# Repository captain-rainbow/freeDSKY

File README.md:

# freeDSKY
My open source DSKY replica that works with ReEntry: an orbital simulator.

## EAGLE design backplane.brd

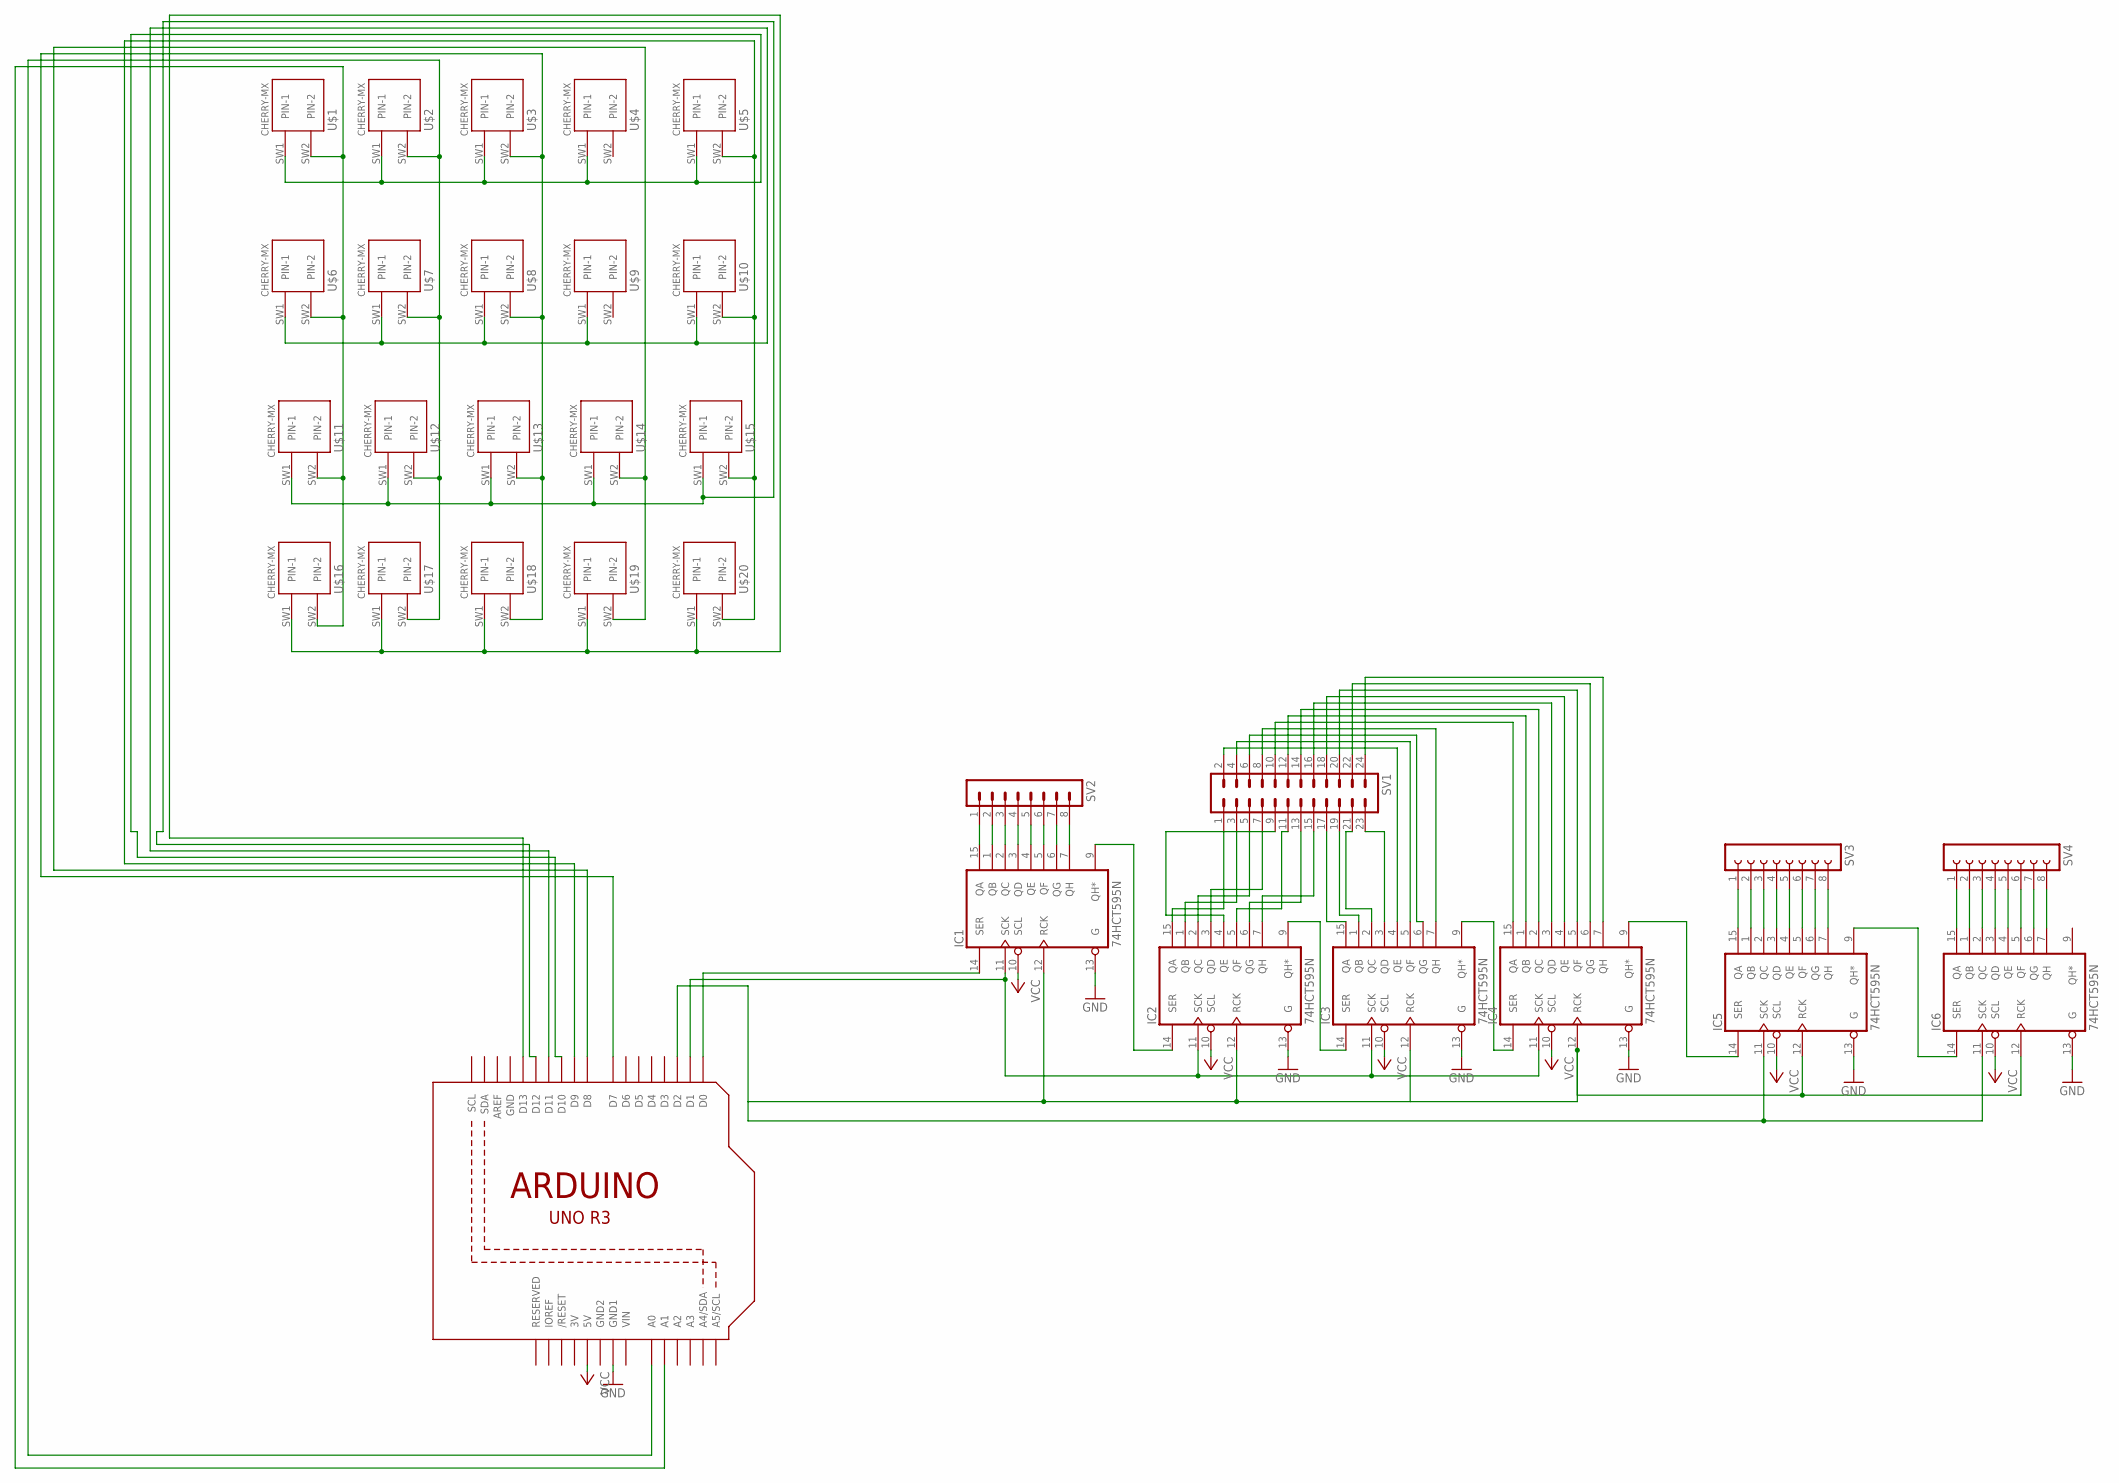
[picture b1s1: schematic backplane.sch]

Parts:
IC1, IC2, IC3, IC4, IC5, IC6: 74HCT595N; DIL16
SV1: MA12-2
SV2: MA08-1
SV3, SV4: FE08-1; FE08
U1: ARDUINOR3-BPLACE
U$1, U$2, U$3, U$4, U$5, U$6, U$7, U$8, U$9, U$10, U$11, U$12, U$13, U$14, U$15, U$16, U$17, U$18, U$19, U$20: CHERRY-MX

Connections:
3V: U1.3V
GND: IC1.8 (GND), IC1.13 (G), IC2.8 (GND), IC2.13 (G), IC3.8 (GND), IC3.13 (G), IC4.8 (GND), IC4.13 (G), IC5.8 (GND), IC5.13 (G), IC6.8 (GND), IC6.13 (G), U1.GND, U1.GND1
GND2: U1.GND2
unnamed: U1.D10, U$1.SW1 (PIN-1), U$2.SW1 (PIN-1), U$3.SW1 (PIN-1), U$4.SW1 (PIN-1), U$5.SW1 (PIN-1)
unnamed: U1.D11, U$6.SW1 (PIN-1), U$7.SW1 (PIN-1), U$8.SW1 (PIN-1), U$9.SW1 (PIN-1), U$10.SW1 (PIN-1)
unnamed: U1.D12, U$11.SW1 (PIN-1), U$12.SW1 (PIN-1), U$13.SW1 (PIN-1), U$14.SW1 (PIN-1), U$15.SW1 (PIN-1)
unnamed: U1.A1, U$1.SW2 (PIN-2), U$6.SW2 (PIN-2), U$11.SW2 (PIN-2), U$16.SW2 (PIN-2)
unnamed: U1.A0, U$2.SW2 (PIN-2), U$7.SW2 (PIN-2), U$12.SW2 (PIN-2), U$17.SW2 (PIN-2)
unnamed: U1.D7, U$3.SW2 (PIN-2), U$8.SW2 (PIN-2), U$13.SW2 (PIN-2), U$18.SW2 (PIN-2)
unnamed: U1.D8, U$14.SW2 (PIN-2), U$19.SW2 (PIN-2)
unnamed: U1.D9, U$5.SW2 (PIN-2), U$10.SW2 (PIN-2), U$15.SW2 (PIN-2), U$20.SW2 (PIN-2)
unnamed: IC3.5 (QF), SV1.4
unnamed: U1.D13, U$16.SW1 (PIN-1), U$17.SW1 (PIN-1), U$18.SW1 (PIN-1), U$19.SW1 (PIN-1), U$20.SW1 (PIN-1)
unnamed: IC3.6 (QG), SV1.6
unnamed: IC3.7 (QH), SV1.8
unnamed: IC2.15 (QA), SV1.1
unnamed: IC2.1 (QB), SV1.3
unnamed: IC2.2 (QC), SV1.5
unnamed: IC2.3 (QD), SV1.7
unnamed: IC2.4 (QE), SV1.9
unnamed: IC2.5 (QF), SV1.11
unnamed: IC2.6 (QG), SV1.13
unnamed: IC2.7 (QH), SV1.15
unnamed: IC3.15 (QA), SV1.17
unnamed: IC3.1 (QB), SV1.19
unnamed: IC3.2 (QC), SV1.21
unnamed: IC3.3 (QD), SV1.23
unnamed: IC3.4 (QE), SV1.2
unnamed: IC4.15 (QA), SV1.10
unnamed: IC4.1 (QB), SV1.12
unnamed: IC4.2 (QC), SV1.14
unnamed: IC4.3 (QD), SV1.16
unnamed: IC4.4 (QE), SV1.18
unnamed: IC4.5 (QF), SV1.20
unnamed: IC4.6 (QG), SV1.22
unnamed: IC4.7 (QH), SV1.24
unnamed: IC1.15 (QA), SV2.1
unnamed: IC1.1 (QB), SV2.2
unnamed: IC1.2 (QC), SV2.3
unnamed: IC1.3 (QD), SV2.4
unnamed: IC1.4 (QE), SV2.5
unnamed: IC1.5 (QF), SV2.6
unnamed: IC1.6 (QG), SV2.7
unnamed: IC1.7 (QH), SV2.8
unnamed: IC1.9 (QH*), IC2.14 (SER)
unnamed: IC2.9 (QH*), IC3.14 (SER)
unnamed: IC3.9 (QH*), IC4.14 (SER)
unnamed: IC1.14 (SER), U1.D0
unnamed: IC1.11 (SCK), IC2.11 (SCK), IC3.11 (SCK), IC4.11 (SCK), U1.D1
unnamed: IC5.15 (QA), SV3.1
unnamed: IC1.12 (RCK), IC2.12 (RCK), IC3.12 (RCK), IC4.12 (RCK), IC5.11 (SCK), IC5.12 (RCK), IC6.11 (SCK), IC6.12 (RCK), U1.D2
unnamed: IC5.1 (QB), SV3.2
unnamed: IC5.2 (QC), SV3.3
unnamed: IC5.3 (QD), SV3.4
unnamed: IC5.4 (QE), SV3.5
unnamed: IC5.5 (QF), SV3.6
unnamed: IC5.6 (QG), SV3.7
unnamed: IC5.7 (QH), SV3.8
unnamed: IC6.15 (QA), SV4.1
unnamed: IC6.1 (QB), SV4.2
unnamed: IC6.2 (QC), SV4.3
unnamed: IC6.3 (QD), SV4.4
unnamed: IC6.4 (QE), SV4.5
unnamed: IC6.5 (QF), SV4.6
unnamed: IC6.6 (QG), SV4.7
unnamed: IC6.7 (QH), SV4.8
unnamed: IC5.9 (QH*), IC6.14 (SER)
unnamed: IC4.9 (QH*), IC5.14 (SER)
VCC: IC1.10 (SCL), IC1.16 (VCC), IC2.10 (SCL), IC2.16 (VCC), IC3.10 (SCL), IC3.16 (VCC), IC4.10 (SCL), IC4.16 (VCC), IC5.10 (SCL), IC5.16 (VCC), IC6.10 (SCL), IC6.16 (VCC), U1.5V
VIN: U1.VIN

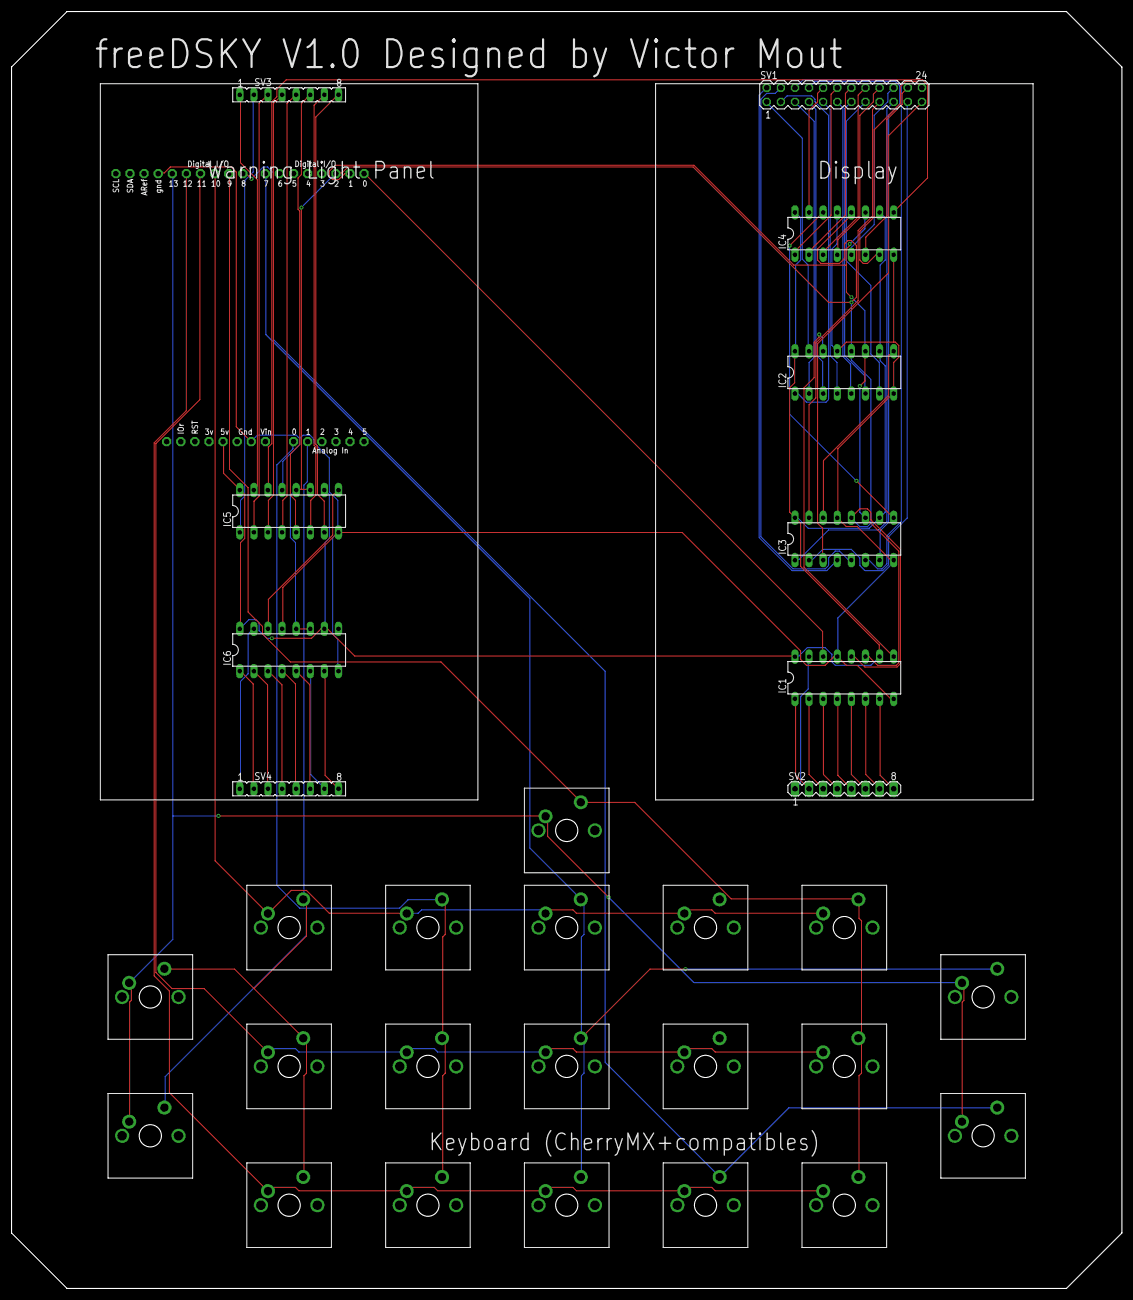
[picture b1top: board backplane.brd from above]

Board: 2 copper layers, 200.0 x 230.0 mm, 31 parts (0 on the bottom side), 67 nets.

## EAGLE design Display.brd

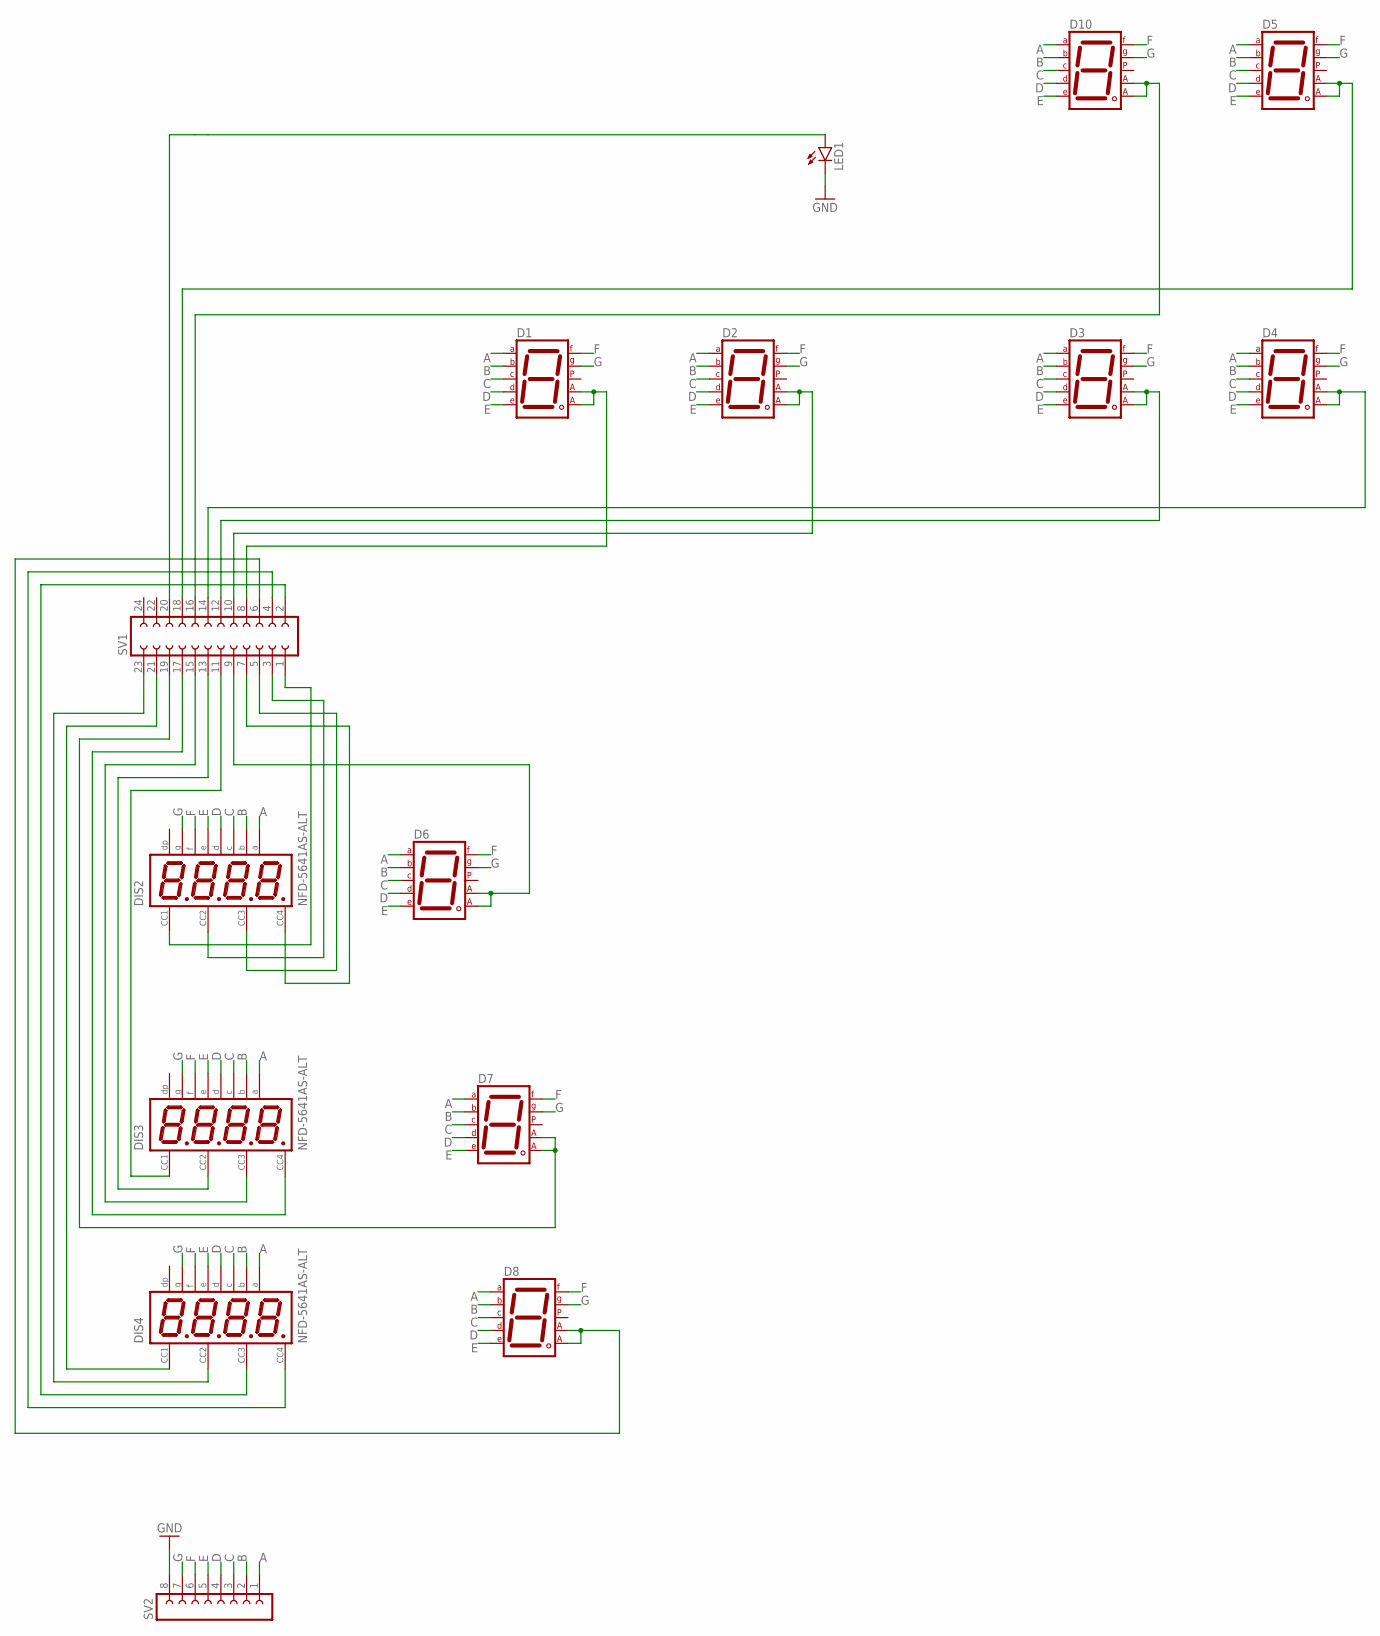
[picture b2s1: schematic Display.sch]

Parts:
D1, D2, D3, D4, D5, D6, D7, D8, D10: 7SEG-CA; 7SEG-13
DIS2, DIS3, DIS4: NFD-5641AS-ALT; NFD-5641
LED1: LED5MM
SV1: FE12-2
SV2: FE08-1; FE08

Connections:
A: D1.7 (A), D2.7 (A), D3.7 (A), D4.7 (A), D5.7 (A), D6.7 (A), D7.7 (A), D8.7 (A), D10.7 (A), DIS2.P$11, DIS3.P$11, DIS4.P$11, SV2.1
B: D1.6 (B), D2.6 (B), D3.6 (B), D4.6 (B), D5.6 (B), D6.6 (B), D7.6 (B), D8.6 (B), D10.6 (B), DIS2.P$7, DIS3.P$7, DIS4.P$7, SV2.2
C: D1.4 (C), D2.4 (C), D3.4 (C), D4.4 (C), D5.4 (C), D6.4 (C), D7.4 (C), D8.4 (C), D10.4 (C), DIS2.P$4, DIS3.P$4, DIS4.P$4, SV2.3
D: D1.2 (D), D2.2 (D), D3.2 (D), D4.2 (D), D5.2 (D), D6.2 (D), D7.2 (D), D8.2 (D), D10.2 (D), DIS2.P$2, DIS3.P$2, DIS4.P$2, SV2.4
E: D1.1 (E), D2.1 (E), D3.1 (E), D4.1 (E), D5.1 (E), D6.1 (E), D7.1 (E), D8.1 (E), D10.1 (E), DIS2.P$1, DIS3.P$1, DIS4.P$1, SV2.5
F: D1.9 (F), D2.9 (F), D3.9 (F), D4.9 (F), D5.9 (F), D6.9 (F), D7.9 (F), D8.9 (F), D10.9 (F), DIS2.P$10, DIS3.P$10, DIS4.P$10, SV2.6
G: D1.10 (G), D2.10 (G), D3.10 (G), D4.10 (G), D5.10 (G), D6.10 (G), D7.10 (G), D8.10 (G), D10.10 (G), DIS2.P$5, DIS3.P$5, DIS4.P$5, SV2.7
GND: LED1.K (C), SV2.8
unnamed: DIS2.P$12, SV1.1
unnamed: DIS2.P$9, SV1.3
unnamed: DIS2.P$8, SV1.5
unnamed: DIS2.P$6, SV1.7
unnamed: D6.3 (CA1), D6.8 (CA2), SV1.9
unnamed: DIS3.P$12, SV1.11
unnamed: DIS3.P$9, SV1.13
unnamed: DIS3.P$8, SV1.15
unnamed: DIS3.P$6, SV1.17
unnamed: D7.3 (CA1), D7.8 (CA2), SV1.19
unnamed: DIS4.P$12, SV1.21
unnamed: DIS4.P$9, SV1.23
unnamed: DIS4.P$8, SV1.2
unnamed: DIS4.P$6, SV1.4
unnamed: D1.3 (CA1), D1.8 (CA2), SV1.8
unnamed: D8.3 (CA1), D8.8 (CA2), SV1.6
unnamed: D2.3 (CA1), D2.8 (CA2), SV1.10
unnamed: D3.3 (CA1), D3.8 (CA2), SV1.12
unnamed: D4.3 (CA1), D4.8 (CA2), SV1.14
unnamed: D10.3 (CA1), D10.8 (CA2), SV1.16
unnamed: D5.3 (CA1), D5.8 (CA2), SV1.18
unnamed: LED1.A, SV1.20

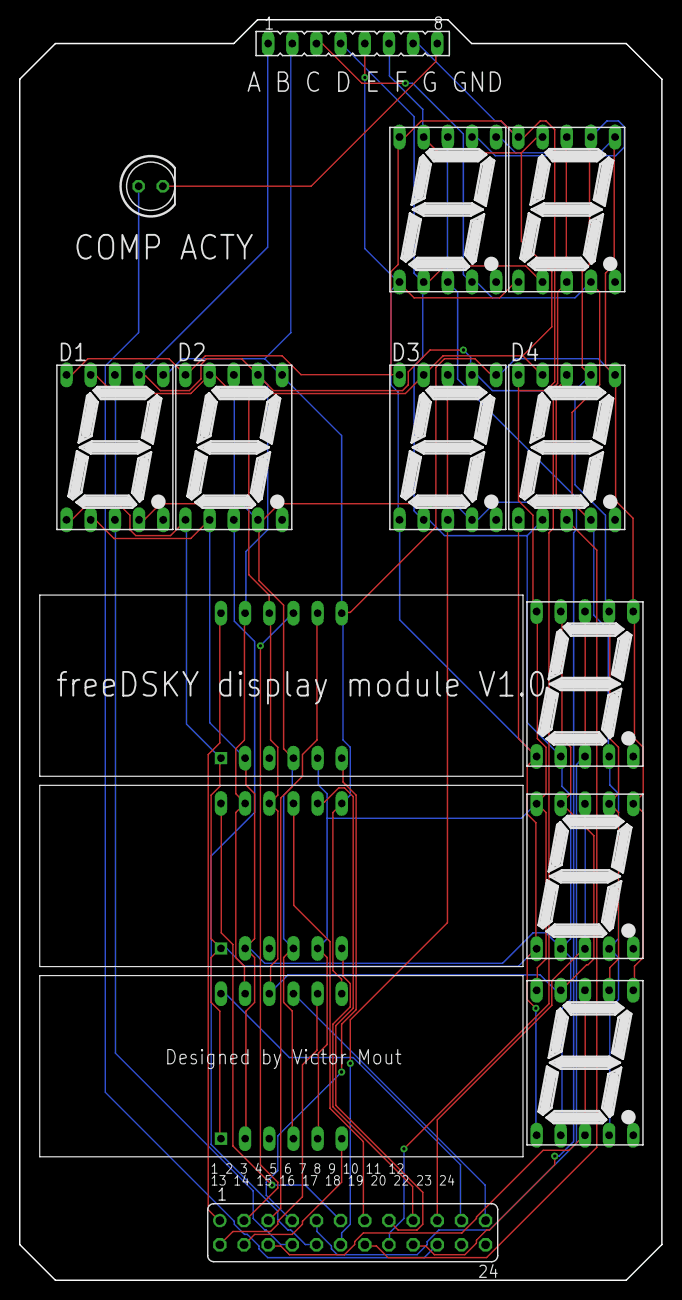
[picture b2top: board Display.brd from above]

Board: 2 copper layers, 67.5 x 132.5 mm, 15 parts (0 on the bottom side), 30 nets.

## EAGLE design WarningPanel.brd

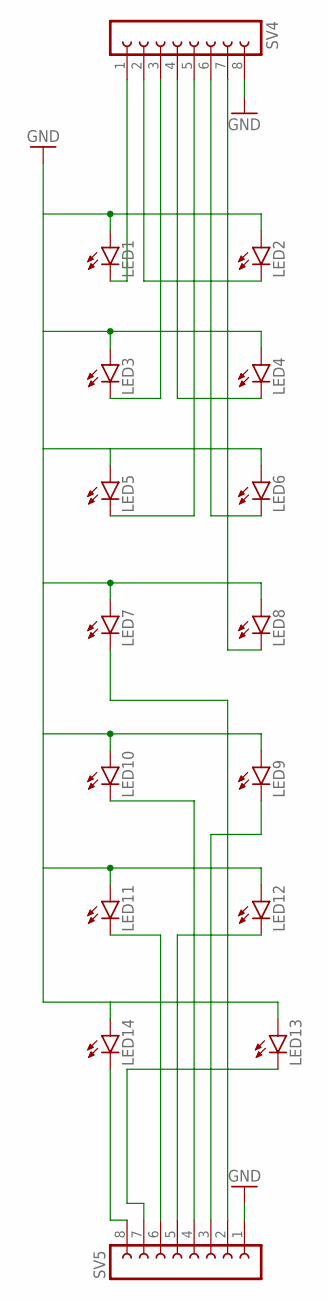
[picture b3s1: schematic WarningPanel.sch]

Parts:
LED1, LED2, LED3, LED4, LED5, LED6, LED7, LED8, LED9, LED10, LED11, LED12, LED13, LED14: LED5MM
SV4, SV5: FE08-1; FE08

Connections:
GND: LED13.A, LED14.A, SV4.8, SV5.1
unnamed: LED1.A, LED2.A
unnamed: LED3.A, LED4.A
unnamed: LED14.K (C), SV5.8
unnamed: LED13.K (C), SV5.7
unnamed: LED5.A, LED6.A
unnamed: LED7.A, LED8.A
unnamed: LED11.K (C), SV5.6
unnamed: LED9.A, LED10.A
unnamed: LED11.A, LED12.A
unnamed: LED12.K (C), SV5.5
unnamed: LED10.K (C), SV5.4
unnamed: LED7.K (C), SV5.2
unnamed: LED1.K (C), SV4.1
unnamed: LED2.K (C), SV4.2
unnamed: LED3.K (C), SV4.3
unnamed: LED4.K (C), SV4.4
unnamed: LED5.K (C), SV4.5
unnamed: LED6.K (C), SV4.6
unnamed: LED8.K (C), SV4.7
unnamed: LED9.K (C), SV5.3

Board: 2 copper layers, 16 parts (3 on the bottom side), 21 nets, no tracks yet.
